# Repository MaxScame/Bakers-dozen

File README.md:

# Baker's dozen👻
#### [This text in russian➡️](https://github.com/MaxScame/Bakers-dozen/blob/master/README_RU.md)

40% ortholinear keyboard

---
### Layout

### PCB

Front:

Back:

---
### License
This project is licensed by [MIT](https://github.com/MaxScame/Bakers-dozen/blob/master/LICENSE)

### Credits
ai03-2725 for
- [MX_Alps_Hybrid](https://github.com/ai03-2725/MX_Alps_Hybrid)
- [random-keyboard-parts.pretty](https://github.com/ai03-2725/random-keyboard-parts.pretty)

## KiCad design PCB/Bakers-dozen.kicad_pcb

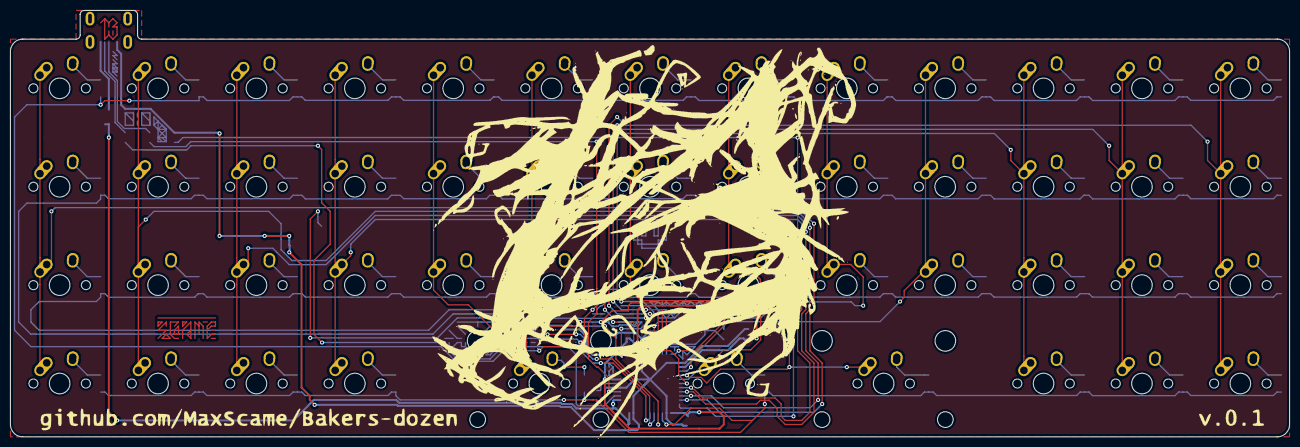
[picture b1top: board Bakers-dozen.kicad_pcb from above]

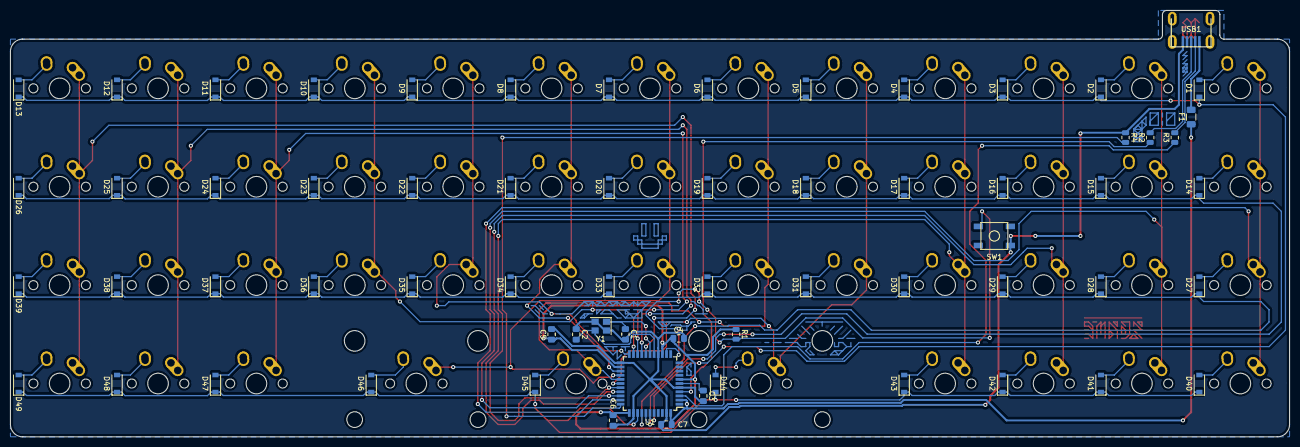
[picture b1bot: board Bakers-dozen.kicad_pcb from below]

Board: 2 copper layers, 247.7 x 82.5 mm, 114 parts (65 on the bottom side), 78 nets.

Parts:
C1, C2: 22pF; C_0805_2012Metric_Pad1.15x1.40mm_HandSolder
C3: 1uF; C_0805_2012Metric_Pad1.15x1.40mm_HandSolder
C4, C5, C6: 0.1uF; C_0805_2012Metric_Pad1.15x1.40mm_HandSolder
C7: 10uF; C_0805_2012Metric_Pad1.15x1.40mm_HandSolder
D1, D2, D3, D4, D5, D6, D7, D8, D9, D10, D11, D12, D13, D14, D15, D16, D17, D18, D19, D20, D21, D22, D23, D24, D25, D26, D27, D28, D29, D30, D31, D32, D33, D34, D35, D36, D37, D38, D39, D40, D41, D42, D43, D44, D45, D46, D47, D48, D49: SOD-123; D_SOD-123
F1: 500mA; Fuse_1206_3216Metric
MX1, MX2, MX3, MX4, MX5, MX6, MX7, MX8, MX9, MX10, MX11, MX12, MX13, MX14, MX15, MX16, MX17, MX18, MX19, MX20, MX21, MX22, MX23, MX24, MX25, MX26, MX27, MX28, MX29, MX30, MX31, MX32, MX33, MX34, MX35, MX36, MX37, MX38, MX39, MX40, MX41, MX42, MX43, MX45, MX47, MX48, MX49: MX-NoLED; MX-1U-NoLED
MX44: MX-NoLED; MX-2.75U-ReversedStabilizers-NoLED
MX46: MX-NoLED; MX-2.25U-ReversedStabilizers-NoLED
R1, R4: 10k; R_0805_2012Metric
R2, R3: 22; R_0805_2012Metric
SW1: SW_Push; SKQG-1155865
U1: ATmega32U4-AU; TQFP-44_10x10mm_P0.8mm
USB1: Molex-0548190589
Y1: 16Mhz; Crystal_SMD_3225-4Pin_3.2x2.5mm

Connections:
+5V: C4.1, C5.1, C6.1, C7.1, F1.1, R1.1, U1.2, U1.7, U1.14, U1.24, U1.34, U1.44
COL0: MX1.1, MX14.1, MX27.1, MX40.1, U1.32
COL1: MX2.1, MX15.1, MX28.1, MX41.1, U1.31
COL2: MX3.1, MX16.1, MX29.1, MX42.1, U1.30
COL3: MX4.1, MX17.1, MX30.1, MX43.1, U1.29
COL4: MX5.1, MX18.1, MX31.1, MX44.1, U1.28
COL5: MX6.1, MX19.1, MX32.1, MX45.1, U1.27
COL6: MX7.1, MX20.1, MX33.1, MX46.1, U1.26
COL7: MX8.1, MX21.1, MX34.1, U1.25
COL8: MX9.1, MX22.1, MX35.1, U1.22
COL9: MX10.1, MX23.1, MX36.1, U1.21
COL10: MX11.1, MX24.1, MX37.1, MX47.1, U1.20
COL11: MX12.1, MX25.1, MX38.1, MX48.1, U1.19
COL12: MX13.1, MX26.1, MX39.1, MX49.1, U1.18
D+: R2.2, USB1.3
D-: R3.2, USB1.4
GND: C1.2, C2.1, C3.2, C4.2, C5.2, C6.2, C7.2, R4.1, SW1.1, U1.5, U1.15, U1.23, U1.35, U1.43, USB1.1, Y1.2, Y1.4
unnamed: C1.1, U1.17, Y1.1
unnamed: C2.2, U1.16, Y1.3
unnamed: C3.1, U1.6
unnamed: D1.2, MX1.2
unnamed: D2.2, MX2.2
unnamed: D3.2, MX3.2
unnamed: D4.2, MX4.2
unnamed: D5.2, MX5.2
unnamed: D6.2, MX6.2
unnamed: D7.2, MX7.2
unnamed: D8.2, MX8.2
unnamed: D9.2, MX9.2
unnamed: D10.2, MX10.2
unnamed: D11.2, MX11.2
unnamed: D12.2, MX12.2
unnamed: D13.2, MX13.2
unnamed: D14.2, MX14.2
unnamed: D15.2, MX15.2
unnamed: D16.2, MX16.2
unnamed: D17.2, MX17.2
unnamed: D18.2, MX18.2
unnamed: D19.2, MX19.2
unnamed: D20.2, MX20.2
unnamed: D21.2, MX21.2
unnamed: D22.2, MX22.2
unnamed: D23.2, MX23.2
unnamed: D24.2, MX24.2
unnamed: D25.2, MX25.2
unnamed: D26.2, MX26.2
unnamed: D27.2, MX27.2
unnamed: D28.2, MX28.2
unnamed: D29.2, MX29.2
unnamed: D30.2, MX30.2
unnamed: D31.2, MX31.2
unnamed: D32.2, MX32.2
unnamed: D33.2, MX33.2
unnamed: D34.2, MX34.2
unnamed: D35.2, MX35.2
unnamed: D36.2, MX36.2
unnamed: D37.2, MX37.2
unnamed: D38.2, MX38.2
unnamed: D39.2, MX39.2
unnamed: D40.2, MX40.2
unnamed: D41.2, MX41.2
unnamed: D42.2, MX42.2
unnamed: D43.2, MX43.2
unnamed: D44.2, MX44.2
unnamed: D45.2, MX45.2
unnamed: D46.2, MX46.2
unnamed: D47.2, MX47.2
unnamed: D48.2, MX48.2
unnamed: D49.2, MX49.2
unnamed: R1.2, SW1.2, U1.13
unnamed: R2.1, U1.4
unnamed: R3.1, U1.3
unnamed: R4.2, U1.33
ROW0: D1.1, D2.1, D3.1, D4.1, D5.1, D6.1, D7.1, D8.1, D9.1, D10.1, D11.1, D12.1, D13.1, U1.39
ROW1: D14.1, D15.1, D16.1, D17.1, D18.1, D19.1, D20.1, D21.1, D22.1, D23.1, D24.1, D25.1, D26.1, U1.38
ROW2: D27.1, D28.1, D29.1, D30.1, D31.1, D32.1, D33.1, D34.1, D35.1, D36.1, D37.1, D38.1, D39.1, U1.37
ROW3: D40.1, D41.1, D42.1, D43.1, D44.1, D45.1, D46.1, D47.1, D48.1, D49.1, U1.36
VCC: F1.2, USB1.5

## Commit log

2020-03-21 Init KiCad Project
    Now, PCB!
2020-03-21 Add submodules
2020-03-21 Add footprint libraries
2020-03-22 Finally create schematic
2020-03-23 Plate size and change footprint
2020-03-23 Trace pcb
2020-03-23 Ground fills
2020-03-24 Create LICENSE
2020-03-24 Add some cosmetic changes
2020-03-25 Flip stabs
2020-03-25 Add russian README
2020-03-25 Set theme jekyll-theme-dinky
2020-03-25 Add gerber files
